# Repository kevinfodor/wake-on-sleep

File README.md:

This project is an implementation of a Wake-On-Sleep device. The idea is that this device will remain idle while it is being played with (motion/activity is detected). However when it has become idle for a period of time, it will wake-up and sound an alert. If someone plays with the device, the alert is cancelled. If nobody acknowledges the device (remains idle) it finally goes back to sleep.

This project is based on the [Wake-On-Shake](https://www.sparkfun.com/products/11447) project, based on a concept by Nitzan Gadish of Analog Devices.
Although the behavior in this case is somewhat opposite. As long as someone is using the device (playing with it) it remains idle. It wakes once someone stops playing with it, sounding an alarm. Thus the name; Wake-On-Sleep.

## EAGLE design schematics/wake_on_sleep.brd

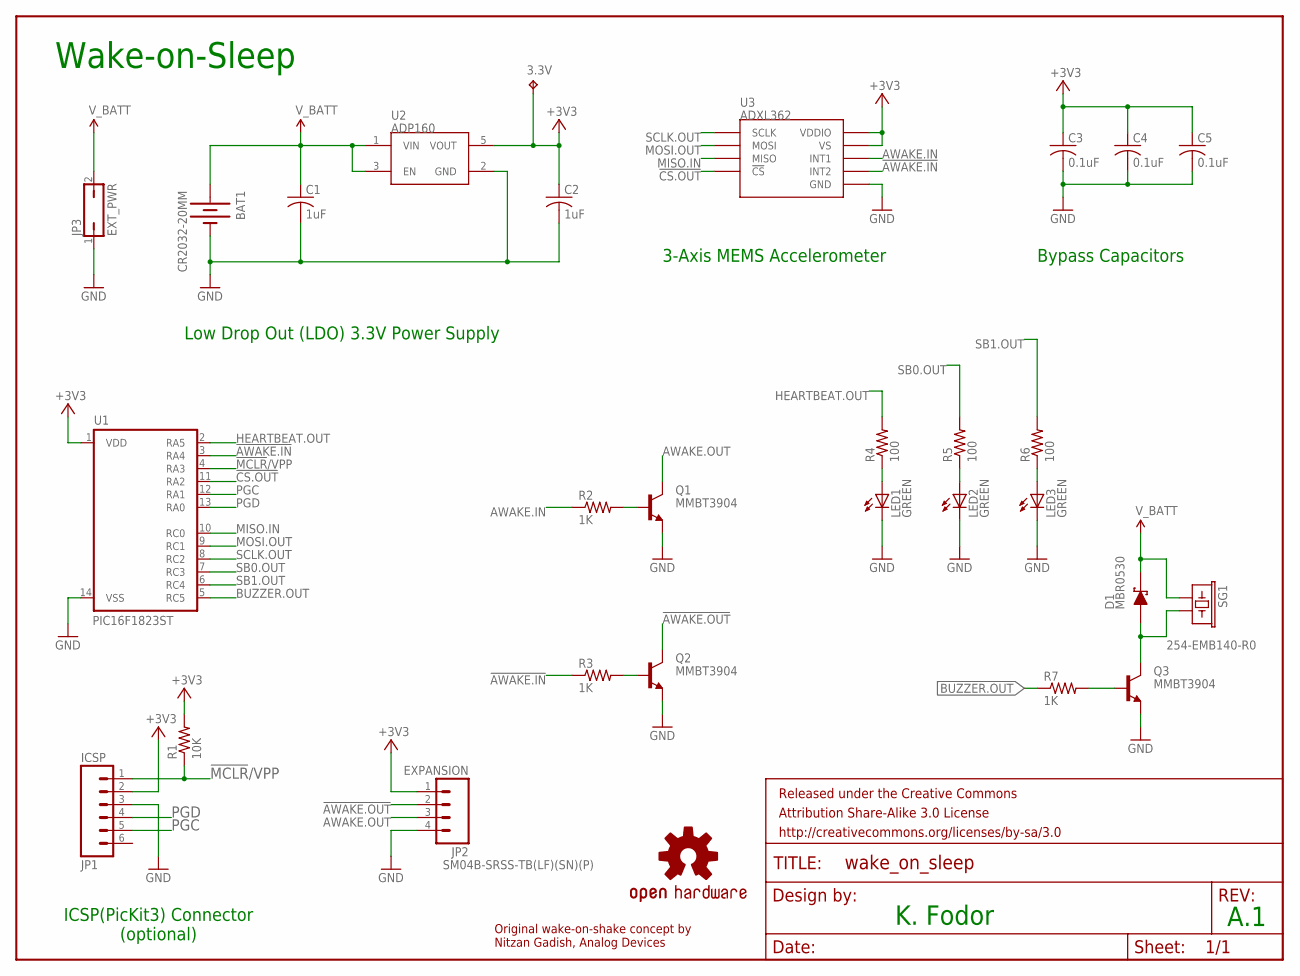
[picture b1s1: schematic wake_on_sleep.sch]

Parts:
3.3V: TPB2,54; B2,54
BAT1: CR2032-20MM; BATTCON_20MM_SMD_EJECT; PARTNO BA2032SM
C1, C2: 1uF; C0603; PARTNO C0603C105K8RACTU
C3, C4, C5: 0.1uF; C0603; PARTNO C0603C104M4RACTU
D1: MBR0530; SOD-123; PARTNO MBR0530
FRAME1: FRAME-LETTER; CREATIVE_COMMONS
JP1: ICSP; 1X06_SMD_MALE; PARTNO 5-146128-4
JP2: EXPANSION; 1X04-1MM-RA; PARTNO SM04B-SRSS-TB(LF)(SN)(P)
JP3: EXT_PWR; JP1; PARTNO 826936-2
LED1, LED2, LED3: GREEN; CHIPLED_0603; PARTNO LTST-C191KGKT
LOGO1: OSHW-LOGOL; OSHW-LOGO-L
Q1, Q2, Q3: MMBT3904; SOT23; PARTNO MMBT3904
R1: 10K; R0603R; PARTNO RK73H1JTTD1002F
R2, R3, R7: 1K; R0603R; PARTNO RK73H1JTTD1001F
R4, R5, R6: 100; R0603R; PARTNO RK73H1JTTD1000F
SG1: BUZZERPTH; BUZZER-12MM; PARTNO 254-EMB140-R0
U1: PIC16F1823ST; TSSOP14; PARTNO PIC16F1823-I/ST
U2: ADP160; SOT23-5; PARTNO ADP160AUJZ-3.3-R7
U3: ADXL362; ADXL362_EXT; PARTNO ADXL362BCCZ-RL

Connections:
!AWAKE.IN: R3.1, U1.3 (RA4), U3.P$9 (INT2)
!AWAKE.OUT: JP2.2, Q2.3 (C)
!CS.OUT: U1.11 (RA2), U3.P$8 (!CS)
!MCLR!/VPP: JP1.1, R1.1, U1.4 (RA3)
+3V3: 3.3V.TP, C2.1, C3.1, C4.1, C5.1, JP1.2, JP2.1, R1.2, U1.1 (VDD), U2.5 (VOUT), U3.P$1 (VDDIO), U3.P$14 (VS)
AWAKE.IN: R2.1, U3.P$11 (INT1)
AWAKE.OUT: JP2.3, Q1.3 (C)
BUZZER.OUT: R7.1, U1.5 (RC5)
GND: BAT1.VCC@2 (-), C1.2, C2.2, C3.2, C4.2, C5.2, JP1.3, JP2.4, JP3.1, LED1.C, LED2.C, LED3.C, Q1.2 (E), Q2.2 (E), Q3.2 (E), U1.14 (VSS), U2.2 (GND), U3.P$12 (GND), U3.P$13 (GND), U3.P$16 (GND)
HEARTBEAT.OUT: R4.2, U1.2 (RA5)
MISO.IN: U1.10 (RC0), U3.P$7 (MISO)
MOSI.OUT: U1.9 (RC1), U3.P$6 (MOSI)
unnamed: LED3.A, R6.1
unnamed: LED2.A, R5.1
unnamed: LED1.A, R4.1
unnamed: Q1.1 (B), R2.2
unnamed: D1.A, Q3.3 (C), SG1.- (2)
unnamed: Q3.1 (B), R7.2
unnamed: Q2.1 (B), R3.2
PGC: JP1.5, U1.12 (RA1)
PGD: JP1.4, U1.13 (RA0)
SB0.OUT: R5.2, U1.7 (RC3)
SB1.OUT: R6.2, U1.6 (RC4)
SCLK.OUT: U1.8 (RC2), U3.P$4 (SCLK)
V_BATT: BAT1.VCC@1 (+), C1.1, D1.C, JP3.2, SG1.+ (1), U2.1 (VIN), U2.3 (EN)

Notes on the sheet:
Original wake-on-shake concept by Nitzan Gadish, Analog Devices
ICSP(PicKit3) Connector (optional)
Low Drop Out (LDO) 3.3V Power Supply
3-Axis MEMS Accelerometer
Bypass Capacitors

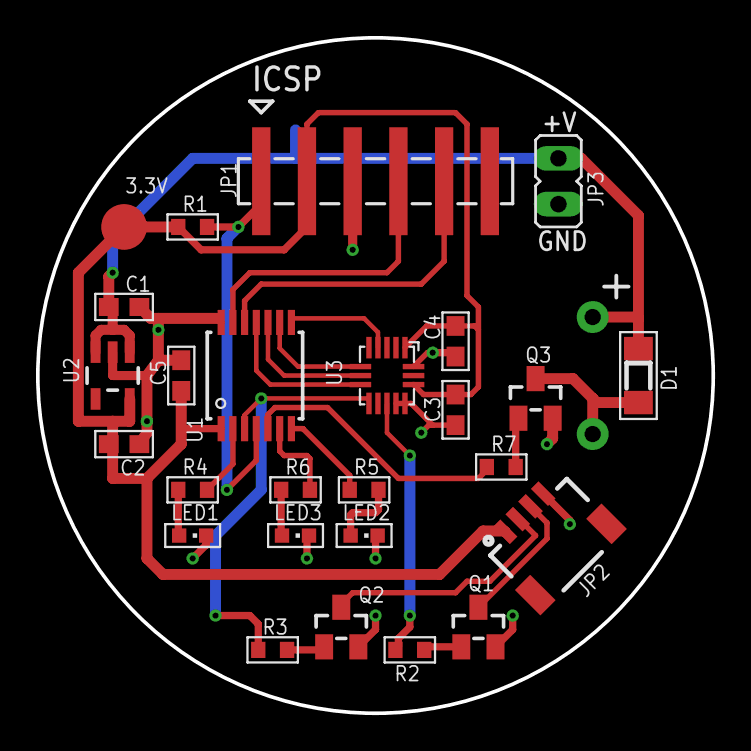
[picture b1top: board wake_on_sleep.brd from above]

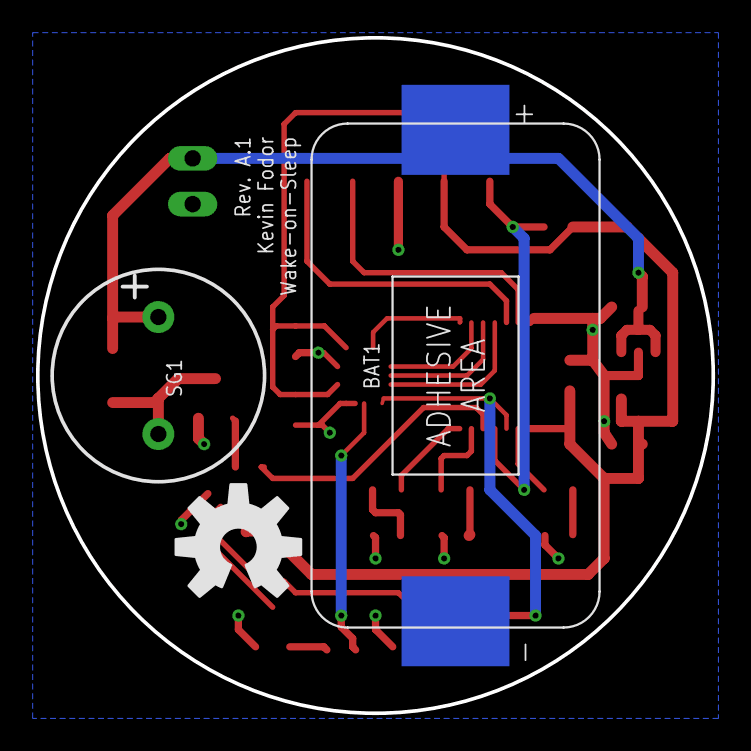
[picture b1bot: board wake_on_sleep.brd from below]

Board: 2 copper layers, 37.5 x 37.5 mm, 30 parts (3 on the bottom side), 25 nets.

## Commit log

2013-09-19 Added block diagram
2013-11-10 Initial drop
2013-12-11 Updated to Rev A.1 and prepared for PCB build
2013-12-14 Updated BOM
2014-04-25 no update
2014-10-24 schematics/eagle.epf view changes
2015-04-07 ./finishGoogleCodeGitHubWikiMigration_edit: Moved ProjectHome.md from wiki branch to README.md in master branch.
2015-05-03 Updated gitignore

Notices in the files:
parts and their libraries:
kevin: Released under the Creative Commons Attribution Share-Alike 3.0 License
kevin: http://creativecommons.org/licenses/by-sa/3.0
kevin: Released under the Creative Commons
